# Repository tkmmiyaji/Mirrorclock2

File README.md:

# Mirrorclock2 --- Through the Looking Glass and How the Digital Clock Looks
# 鏡の国のデジタル時計  Ver. 2.2 b 

### by Homebrew and Electronics Lab Cosmic Web, 16 Jul, 2026

## Summary
This repository contains the hardware designs (KiCAD) and the software (AVR assembly language). The hardware design and software are distributed with the Beerware license. See LICENSE.md  

## Hardware

The KiCAD Ver. 10 project files (incl.  kicad_pro, kicad_pcb, and kicad_sch files are included with necessary ./KiCAD.

* AVR: The 28-dip pachage of the Atmega48,88,168,328 and variants should work. 
* The resistor footprints on the PCB accept either THT (3 DIP pitches/7.62mm between holes) or SMD (1206) components. The LED footprints accept 3mm, 5mm diameter ones that have one DIP pitch (2.54mm) between leads. You may be able to place SMD LEDs if you dare.
* Place the tilt switch diagonally, so that the display is stably in the normal mode (see below) when it is placed on a level surface. See ./Gallery/Tilt_Switch_small.jpg.

### Hard-to-find components

* The temperature-compensated Crytsal Module Kyocera KTXO-18 (12.8MHz) or Mercury VCTCXO VM39S5G is used. The latter can be purchased at Akizuki Denshi Tsuusho in Akihabara, Tokyo (https://akizukidenshi.com/catalog/g/g107275/) (availbale as of July, 2026). There may be easier-to find equivalent SMD parts, but to use these a modification in the PCB footprint is required.  

## Software AVRClock2

This software is written in the assmbly language and can be compiled with avra (https://github.com/Ro5bert/avra) and uploaded to the chip using avrdude (https://github.com/avrdudes/avrdude/), both included in the standard repositories of many Linux distros.

### How to Compile/Install (Linux)
* Install avrdude and avra to your system.
* Connect an ISP programmer to the ISP header (6-pin) on board. Watch the orientation. Match the ISP connector bump to that of the PCB drawing.
* Go to directory: ./AVRA
* Open Makefile in your editor and edit the lines with "MCU_TARGET =" and "PROGRAMMER =" to your chip and programmer respectively. Check the port where the programmer is connected and adjust the PORT=/dev/ttyUSB0 line if needed.
* Also the LED brightness auto-adjustment parameters can be set by editing "FA_LIM =" and "BR_LIM =" lines. See Makefile comments for more explanations. 
* From the shell: <br>
SHELL>make                # This compiles the program. <br>
SHELL>make install        # This installs (uploads) the binary to the chip. <br>

## Usage Instructions 
* Connect an external 12V power source.
* It is highly recommended to connect a 9V rectangular battery (called 006P in Japan) for time backup.
* When the unit turns on or reset with the RST button, the clock displays 00:00 00. The clock starts running.
* __Time Adjustment:__ There are three buttons aligned vertically. With a long (~2 sec) push of the central button (MODE), the system enters the hour adjustment mode. Dots in the hour zone blink. You can adjust hours by pushing the upper (ADJ_FWD) and/or lower (ADJ_BWD) buttons. One more pressing of the central button leads to the minute adjustment mode. Dots in the minute zone blink. Use the ADJ_FWD and/or ADJ_BWD buttons to adjust the minute. Note that a long push **will not** make the forward/backward move fast. Whenever the minute is changed, the second zone is reset to zero. When you want to adjust the clock to a second level, push the ADJ_FWD/ADJ_BWD button at the exact moment the reference clock ticks a zero second.
* One more push of the MODE will return the clock to the normal mode.
* __LED Check:__ In the normal mode, pressing the upper button will turn on all the LEDs.
* LED brightness changes responding to the ambient brightness. A press of the lower button shows some calibration and brightness information. There is a trimpot for limited adjustments of the ambient-to-LED brightness relation. Wider range of adjustment is possible in the software (See above).
* __Normal Mode:__ When the clock is right-side up or on a level surface (i.e. the HH:MM display is above the circuts), it displays the clock normally.
* __Mirror Mode: Turn the clock upside down and look through a mirror!__ The roles of ADJ_FWD and ADJ_BWD buttons are also exchanged in the time adjustment.

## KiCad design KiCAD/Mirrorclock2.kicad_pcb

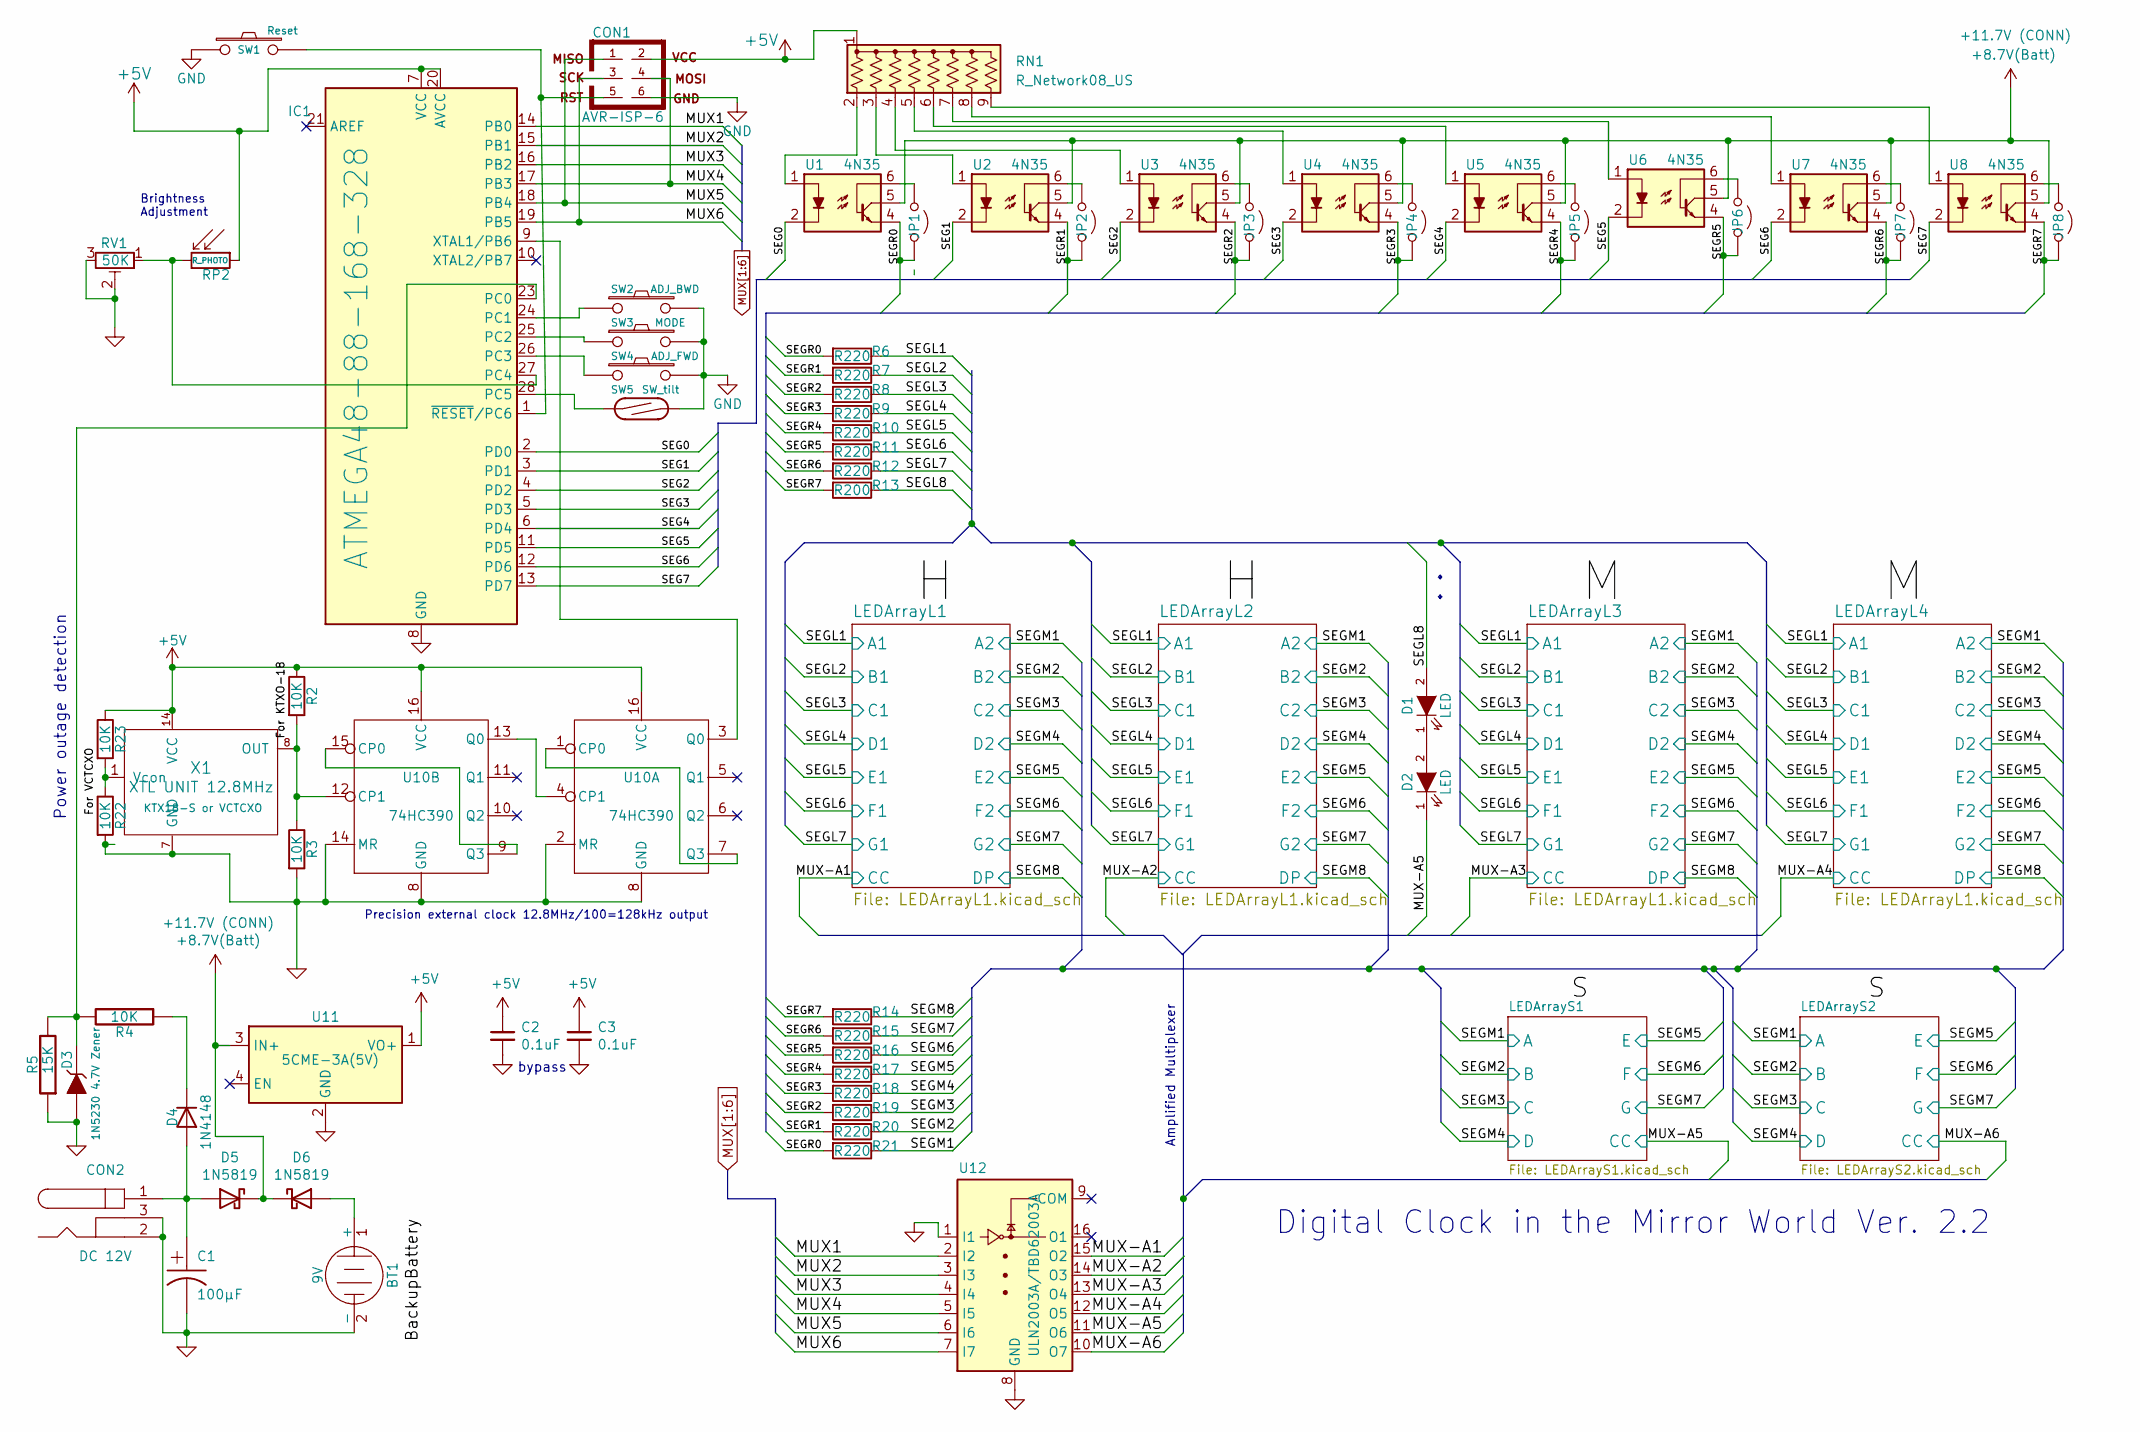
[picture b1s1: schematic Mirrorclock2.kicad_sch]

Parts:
BT1: 9V; PinHeader_1x02_P2.54mm_Vertical
C1: 100μF; CP_Radial_D6.3mm_P2.50mm
C2, C3: 0.1uF; C_Disc_D3.4mm_W2.1mm_P2.50mm
CON1: AVR-ISP-6; AVRISP-6P
CON2: DC 12V; BarrelJack_Horizontal
D1, D2: LED; LED_MULTI
D3: 1N5230 4.7V Zener; D_DO-34_SOD68_P7.62mm_Horizontal
D4: 1N4148; D_DO-35_SOD27_P7.62mm_Horizontal
D5, D6: 1N5819; D_DO-41_SOD81_P7.62mm_Horizontal
IC1: ATMEGA48-88-168-328; DIP-28_W7.62mm
JP1, JP2, JP3, JP4, JP5, JP6, JP7, JP8: Jumper_2_Open; SolderJumper-2_P1.3mm_Open_RoundedPad1.0x1.5mm
R2, R3, R4, R22, R23: 10K; R_THT_SMD1206
R5: 15K; R_THT_SMD1206
R6, R7, R8, R9, R10, R11, R12, R14, R15, R16, R17, R18, R19, R20, R21: R220; R_THT_SMD1206
R13: R200; R_THT_SMD1206
RN1: R_Network08_US; R_Array_SIP9
RP2: R_PHOTO; R_LDR_5.1x4.3mm_P3.4mm_Vertical
RV1: 50K; Potentiometer_Runtron_RM-065_Vertical
SW1: Reset; SW_PUSH_6mm
SW2: ADJ_BWD; SW_PUSH-12mm_Wuerth-430476085716
SW3: MODE; SW_PUSH-12mm_Wuerth-430476085716
SW4: ADJ_FWD; SW_PUSH-12mm_Wuerth-430476085716
SW5: SW_tilt; Sw_tilt_holes
U1, U2, U3, U4, U5, U6, U7, U8: 4N35; DIP-6_W7.62mm
U10: 74HC390; DIP-16_W7.62mm
U11: 5CME-3A(5V); DCDC-Module-Drok
U12: ULN2003A/TBD62003A; DIP-16_W7.62mm
X1: XTL UNIT 12.8MHz; Crystal_M39S_KTXO18; Part KTX18-S or VCTCXO

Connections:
+5V: C2.1, C3.1, CON1.2, IC1.7 (VCC), IC1.20 (AVCC), R2.1, R23.1, RN1.1 (common), RP2.1, U10.16 (VCC), U11.1 (VO+), X1.14 (VCC)
+12V: D5.1 (K), D6.1 (K), U1.5, U2.5, U3.5, U4.5, U5.5, U6.5, U7.5, U8.5, U11.3 (IN+)
/MUX1: IC1.14 (PB0), U12.2 (I2)
/MUX2: IC1.15 (PB1), U12.3 (I3)
/MUX3: IC1.16 (PB2), U12.4 (I4)
/MUX4: CON1.4, IC1.17 (PB3), U12.5 (I5)
/MUX5: CON1.1, IC1.18 (PB4), U12.6 (I6)
/MUX6: CON1.3, IC1.19 (PB5), U12.7 (I7)
/MUX-A1: U12.15 (O2); also elsewhere on the board
/MUX-A2: U12.14 (O3); also elsewhere on the board
/MUX-A3: U12.13 (O4); also elsewhere on the board
/MUX-A4: U12.12 (O5); also elsewhere on the board
/MUX-A5: D2.1 (K), U12.11 (O6); also elsewhere on the board
/MUX-A6: U12.10 (O7); also elsewhere on the board
/SEG0: IC1.2 (PD0), U1.2
/SEG1: IC1.3 (PD1), U2.2
/SEG2: IC1.4 (PD2), U3.2
/SEG3: IC1.5 (PD3), U4.2
/SEG4: IC1.6 (PD4), U5.2
/SEG5: IC1.11 (PD5), U6.2
/SEG6: IC1.12 (PD6), U7.2
/SEG7: IC1.13 (PD7), U8.2
/SEGL1: R6.1; also elsewhere on the board
/SEGL2: R7.1; also elsewhere on the board
/SEGL3: R8.1; also elsewhere on the board
/SEGL4: R9.1; also elsewhere on the board
/SEGL5: R10.1; also elsewhere on the board
/SEGL6: R11.1; also elsewhere on the board
/SEGL7: R12.1; also elsewhere on the board
/SEGL8: D1.2 (A), R13.1
/SEGM1: R21.1; also elsewhere on the board
/SEGM2: R20.1; also elsewhere on the board
/SEGM3: R19.1; also elsewhere on the board
/SEGM4: R18.1; also elsewhere on the board
/SEGM5: R17.1; also elsewhere on the board
/SEGM6: R16.1; also elsewhere on the board
/SEGM7: R15.1; also elsewhere on the board
/SEGM8: R14.1; also elsewhere on the board
/SEGR0: JP1.2 (B), R6.2, R21.2, U1.4
/SEGR1: JP2.2 (B), R7.2, R20.2, U2.4
/SEGR2: JP3.2 (B), R8.2, R19.2, U3.4
/SEGR3: JP4.2 (B), R9.2, R18.2, U4.4
/SEGR4: JP5.2 (B), R10.2, R17.2, U5.4
/SEGR5: JP6.2 (B), R11.2, R16.2, U6.4
/SEGR6: JP7.2 (B), R12.2, R15.2, U7.4
/SEGR7: JP8.2 (B), R13.2, R14.2, U8.4
GND: BT1.2 (-), C1.2, C2.2, C3.2, CON1.6, CON2.2, CON2.3, D3.2 (A), IC1.8 (GND), IC1.22 (GND), R3.2, R5.1, R22.2, RV1.2, RV1.3, SW1.1, SW2.2, SW3.2, SW4.2, SW5.2, U10.2 (MR), U10.8 (GND), U10.14 (MR), U11.2 (GND), U12.1 (I1), U12.8 (GND), X1.7 (GND)
unnamed: BT1.1 (+), D6.2 (A)
unnamed: D1.1 (K), D2.2 (A)
unnamed: D3.1 (K), IC1.23 (PC0), R4.2, R5.2
unnamed: C1.1, CON2.1, D4.2 (A), D5.2 (A)
unnamed: D4.1 (K), R4.1
unnamed: IC1.24 (PC1), SW2.1
unnamed: IC1.25 (PC2), SW3.1
unnamed: IC1.26 (PC3), SW4.1
unnamed: IC1.9 (XTAL1/PB6), U10.3 (Q0)
unnamed: CON1.5, IC1.1 (~RESET/PC6), SW1.2
unnamed: JP1.1 (A), U1.6
unnamed: JP2.1 (A), U2.6
unnamed: JP3.1 (A), U3.6
unnamed: JP4.1 (A), U4.6
unnamed: JP5.1 (A), U5.6
unnamed: JP6.1 (A), U6.6
unnamed: JP7.1 (A), U7.6
unnamed: JP8.1 (A), U8.6
unnamed: RN1.2 (R1), U1.1
unnamed: RN1.3 (R2), U2.1
unnamed: RN1.4 (R3), U3.1
unnamed: RN1.5 (R4), U4.1
unnamed: RN1.6 (R5), U5.1
unnamed: RN1.7 (R6), U6.1
unnamed: RN1.8 (R7), U7.1
unnamed: RN1.9 (R8), U8.1
unnamed: U10.1 (CP0), U10.7 (Q3)
unnamed: U10.4 (CP1), U10.13 (Q0)
unnamed: U10.9 (Q3), U10.15 (CP0)
unnamed: R2.2, R3.1, U10.12 (CP1), X1.8 (OUT)
unnamed: R22.1, R23.2, X1.1 (Vcon)

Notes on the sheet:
Digital Clock in the Mirror World Ver. 2.2
Precision external clock 12.8MHz/100=128kHz output
Brightness Adjustment
Amplified Multiplexer
bypass
Power outage detection

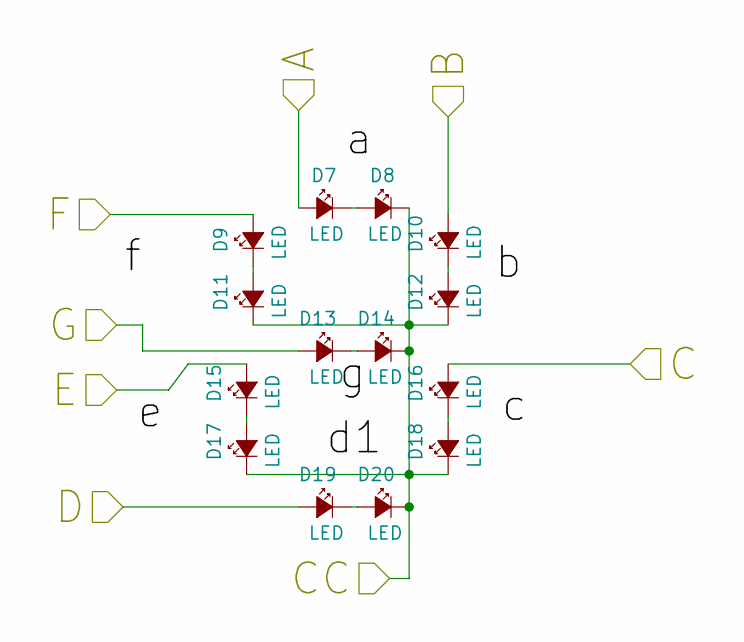
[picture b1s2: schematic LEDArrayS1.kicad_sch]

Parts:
D7, D8, D9, D10, D11, D12, D13, D14, D15, D16, D17, D18, D19, D20: LED; LED_MULTI

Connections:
/MUX-A5: D8.1 (K), D11.1 (K), D12.1 (K), D14.1 (K), D17.1 (K), D18.1 (K), D20.1 (K); also elsewhere on the board
/SEGM1: D7.2 (A); also elsewhere on the board
/SEGM2: D10.2 (A); also elsewhere on the board
/SEGM3: D16.2 (A); also elsewhere on the board
/SEGM4: D19.2 (A); also elsewhere on the board
/SEGM5: D15.2 (A); also elsewhere on the board
/SEGM6: D9.2 (A); also elsewhere on the board
/SEGM7: D13.2 (A); also elsewhere on the board
unnamed: D7.1 (K), D8.2 (A)
unnamed: D10.1 (K), D12.2 (A)
unnamed: D9.1 (K), D11.2 (A)
unnamed: D13.1 (K), D14.2 (A)
unnamed: D15.1 (K), D17.2 (A)
unnamed: D16.1 (K), D18.2 (A)
unnamed: D19.1 (K), D20.2 (A)

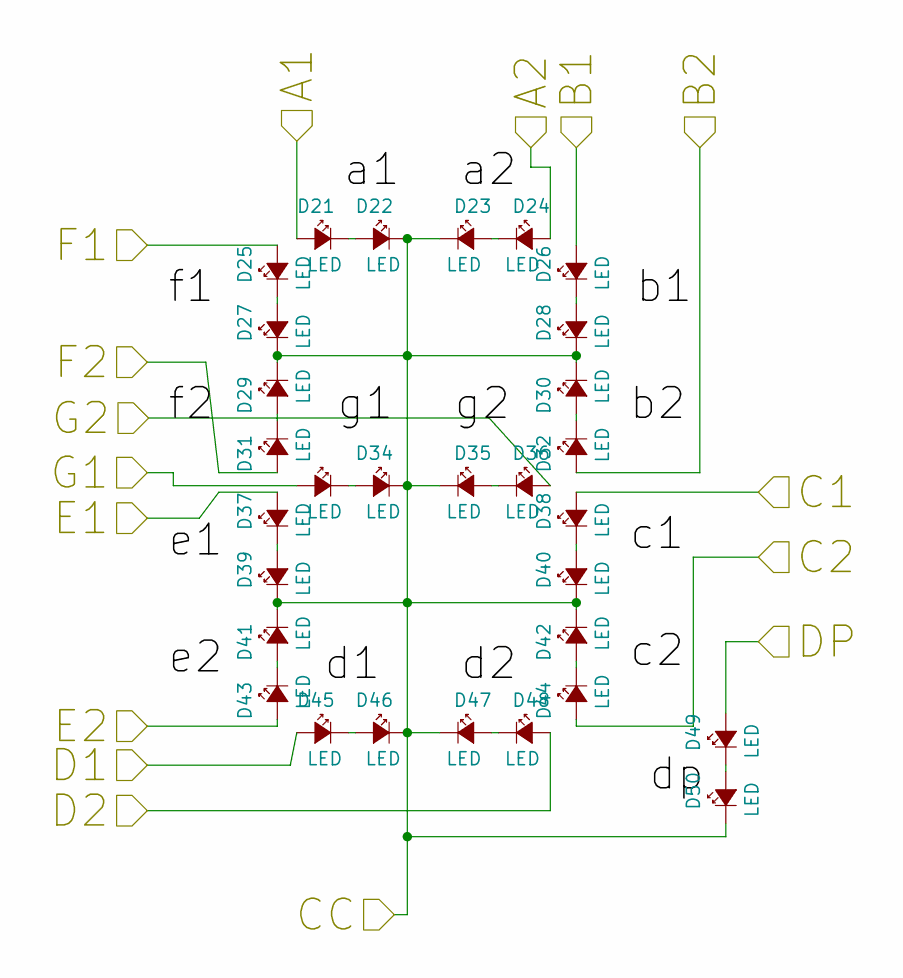
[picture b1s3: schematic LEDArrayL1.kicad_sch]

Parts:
D21, D22, D23, D24, D25, D26, D27, D28, D29, D30, D31, D32, D33, D34, D35, D36, D37, D38, D39, D40, D41, D42, D43, D44, D45, D46, D47, D48: LED; LED_MULTI
D49, D50: LED; LED_MULTI_SIMPLE

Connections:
/MUX-A1: D22.1 (K), D23.1 (K), D27.1 (K), D28.1 (K), D29.1 (K), D30.1 (K), D34.1 (K), D35.1 (K), D39.1 (K), D40.1 (K), D41.1 (K), D42.1 (K), D46.1 (K), D47.1 (K), D50.1 (K); also elsewhere on the board
/SEGL1: D21.2 (A); also elsewhere on the board
/SEGL2: D26.2 (A); also elsewhere on the board
/SEGL3: D38.2 (A); also elsewhere on the board
/SEGL4: D45.2 (A); also elsewhere on the board
/SEGL5: D37.2 (A); also elsewhere on the board
/SEGL6: D25.2 (A); also elsewhere on the board
/SEGL7: D33.2 (A); also elsewhere on the board
/SEGM1: D24.2 (A); also elsewhere on the board
/SEGM2: D32.2 (A); also elsewhere on the board
/SEGM3: D44.2 (A); also elsewhere on the board
/SEGM4: D48.2 (A); also elsewhere on the board
/SEGM5: D43.2 (A); also elsewhere on the board
/SEGM6: D31.2 (A); also elsewhere on the board
/SEGM7: D36.2 (A); also elsewhere on the board
/SEGM8: D49.2 (A); also elsewhere on the board
unnamed: D21.1 (K), D22.2 (A)
unnamed: D23.2 (A), D24.1 (K)
unnamed: D25.1 (K), D27.2 (A)
unnamed: D26.1 (K), D28.2 (A)
unnamed: D29.2 (A), D31.1 (K)
unnamed: D30.2 (A), D32.1 (K)
unnamed: D33.1 (K), D34.2 (A)
unnamed: D35.2 (A), D36.1 (K)
unnamed: D37.1 (K), D39.2 (A)
unnamed: D38.1 (K), D40.2 (A)
unnamed: D41.2 (A), D43.1 (K)
unnamed: D42.2 (A), D44.1 (K)
unnamed: D45.1 (K), D46.2 (A)
unnamed: D47.2 (A), D48.1 (K)
unnamed: D49.1 (K), D50.2 (A)

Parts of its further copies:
D51, D52, D53, D54, D55, D56, D57, D58, D59, D60, D61, D62, D63, D64, D65, D66, D67, D68, D69, D70, D71, D72, D73, D74, D75, D76, D77, D78, D81, D82, D83, D84, D85, D86, D87, D88, D89, D90, D91, D92, D93, D94, D95, D96, D97, D98, D99, D100, D101, D102, D103, D104, D105, D106, D107, D108, D111, D112, D113, D114, D115, D116, D117, D118, D119, D120, D121, D122, D123, D124, D125, D126, D127, D128, D129, D130, D131, D132, D133, D134, D135, D136, D137, D138: LED; LED_MULTI
D79, D80, D109, D110, D139, D140: LED; LED_MULTI_SIMPLE

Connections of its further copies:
/MUX-A2: D52.1 (K), D53.1 (K), D57.1 (K), D58.1 (K), D59.1 (K), D60.1 (K), D64.1 (K), D65.1 (K), D69.1 (K), D70.1 (K), D71.1 (K), D72.1 (K), D76.1 (K), D77.1 (K), D80.1 (K); also elsewhere on the board
/MUX-A3: D82.1 (K), D83.1 (K), D87.1 (K), D88.1 (K), D89.1 (K), D90.1 (K), D94.1 (K), D95.1 (K), D99.1 (K), D100.1 (K), D101.1 (K), D102.1 (K), D106.1 (K), D107.1 (K), D110.1 (K); also elsewhere on the board
/MUX-A4: D112.1 (K), D113.1 (K), D117.1 (K), D118.1 (K), D119.1 (K), D120.1 (K), D124.1 (K), D125.1 (K), D129.1 (K), D130.1 (K), D131.1 (K), D132.1 (K), D136.1 (K), D137.1 (K), D140.1 (K); also elsewhere on the board
/SEGL1: D51.2 (A), D81.2 (A), D111.2 (A); also elsewhere on the board
/SEGL2: D56.2 (A), D86.2 (A), D116.2 (A); also elsewhere on the board
/SEGL3: D68.2 (A), D98.2 (A), D128.2 (A); also elsewhere on the board
/SEGL4: D75.2 (A), D105.2 (A), D135.2 (A); also elsewhere on the board
/SEGL5: D67.2 (A), D97.2 (A), D127.2 (A); also elsewhere on the board
/SEGL6: D55.2 (A), D85.2 (A), D115.2 (A); also elsewhere on the board
/SEGL7: D63.2 (A), D93.2 (A), D123.2 (A); also elsewhere on the board
/SEGM1: D54.2 (A), D84.2 (A), D114.2 (A); also elsewhere on the board
/SEGM2: D62.2 (A), D92.2 (A), D122.2 (A); also elsewhere on the board
/SEGM3: D74.2 (A), D104.2 (A), D134.2 (A); also elsewhere on the board
/SEGM4: D78.2 (A), D108.2 (A), D138.2 (A); also elsewhere on the board
/SEGM5: D73.2 (A), D103.2 (A), D133.2 (A); also elsewhere on the board
/SEGM6: D61.2 (A), D91.2 (A), D121.2 (A); also elsewhere on the board
/SEGM7: D66.2 (A), D96.2 (A), D126.2 (A); also elsewhere on the board
/SEGM8: D79.2 (A), D109.2 (A), D139.2 (A); also elsewhere on the board
unnamed: D51.1 (K), D52.2 (A)
unnamed: D53.2 (A), D54.1 (K)
unnamed: D55.1 (K), D57.2 (A)
unnamed: D56.1 (K), D58.2 (A)
unnamed: D59.2 (A), D61.1 (K)
unnamed: D60.2 (A), D62.1 (K)
unnamed: D63.1 (K), D64.2 (A)
unnamed: D65.2 (A), D66.1 (K)
unnamed: D67.1 (K), D69.2 (A)
unnamed: D68.1 (K), D70.2 (A)
unnamed: D71.2 (A), D73.1 (K)
unnamed: D72.2 (A), D74.1 (K)
unnamed: D75.1 (K), D76.2 (A)
unnamed: D77.2 (A), D78.1 (K)
unnamed: D79.1 (K), D80.2 (A)
unnamed: D81.1 (K), D82.2 (A)
unnamed: D83.2 (A), D84.1 (K)
unnamed: D85.1 (K), D87.2 (A)
unnamed: D86.1 (K), D88.2 (A)
unnamed: D89.2 (A), D91.1 (K)
unnamed: D90.2 (A), D92.1 (K)
unnamed: D93.1 (K), D94.2 (A)
unnamed: D95.2 (A), D96.1 (K)
unnamed: D97.1 (K), D99.2 (A)
unnamed: D98.1 (K), D100.2 (A)
unnamed: D101.2 (A), D103.1 (K)
unnamed: D102.2 (A), D104.1 (K)
unnamed: D105.1 (K), D106.2 (A)
unnamed: D107.2 (A), D108.1 (K)
unnamed: D109.1 (K), D110.2 (A)
unnamed: D111.1 (K), D112.2 (A)
unnamed: D113.2 (A), D114.1 (K)
unnamed: D115.1 (K), D117.2 (A)
unnamed: D116.1 (K), D118.2 (A)
unnamed: D119.2 (A), D121.1 (K)
unnamed: D120.2 (A), D122.1 (K)
unnamed: D123.1 (K), D124.2 (A)
unnamed: D125.2 (A), D126.1 (K)
unnamed: D127.1 (K), D129.2 (A)
unnamed: D128.1 (K), D130.2 (A)
unnamed: D131.2 (A), D133.1 (K)
unnamed: D132.2 (A), D134.1 (K)
unnamed: D135.1 (K), D136.2 (A)
unnamed: D137.2 (A), D138.1 (K)
unnamed: D139.1 (K), D140.2 (A)

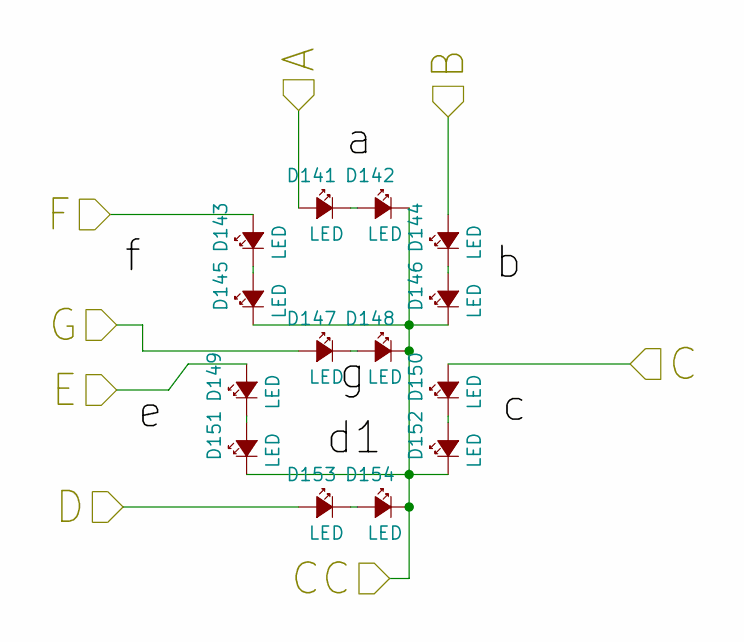
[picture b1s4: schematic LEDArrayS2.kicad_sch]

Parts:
D141, D142, D143, D144, D145, D146, D147, D148, D149, D150, D151, D152, D153, D154: LED; LED_MULTI

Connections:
/MUX-A6: D142.1 (K), D145.1 (K), D146.1 (K), D148.1 (K), D151.1 (K), D152.1 (K), D154.1 (K); also elsewhere on the board
/SEGM1: D141.2 (A); also elsewhere on the board
/SEGM2: D144.2 (A); also elsewhere on the board
/SEGM3: D150.2 (A); also elsewhere on the board
/SEGM4: D153.2 (A); also elsewhere on the board
/SEGM5: D149.2 (A); also elsewhere on the board
/SEGM6: D143.2 (A); also elsewhere on the board
/SEGM7: D147.2 (A); also elsewhere on the board
unnamed: D141.1 (K), D142.2 (A)
unnamed: D143.1 (K), D145.2 (A)
unnamed: D144.1 (K), D146.2 (A)
unnamed: D147.1 (K), D148.2 (A)
unnamed: D149.1 (K), D151.2 (A)
unnamed: D150.1 (K), D152.2 (A)
unnamed: D153.1 (K), D154.2 (A)

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
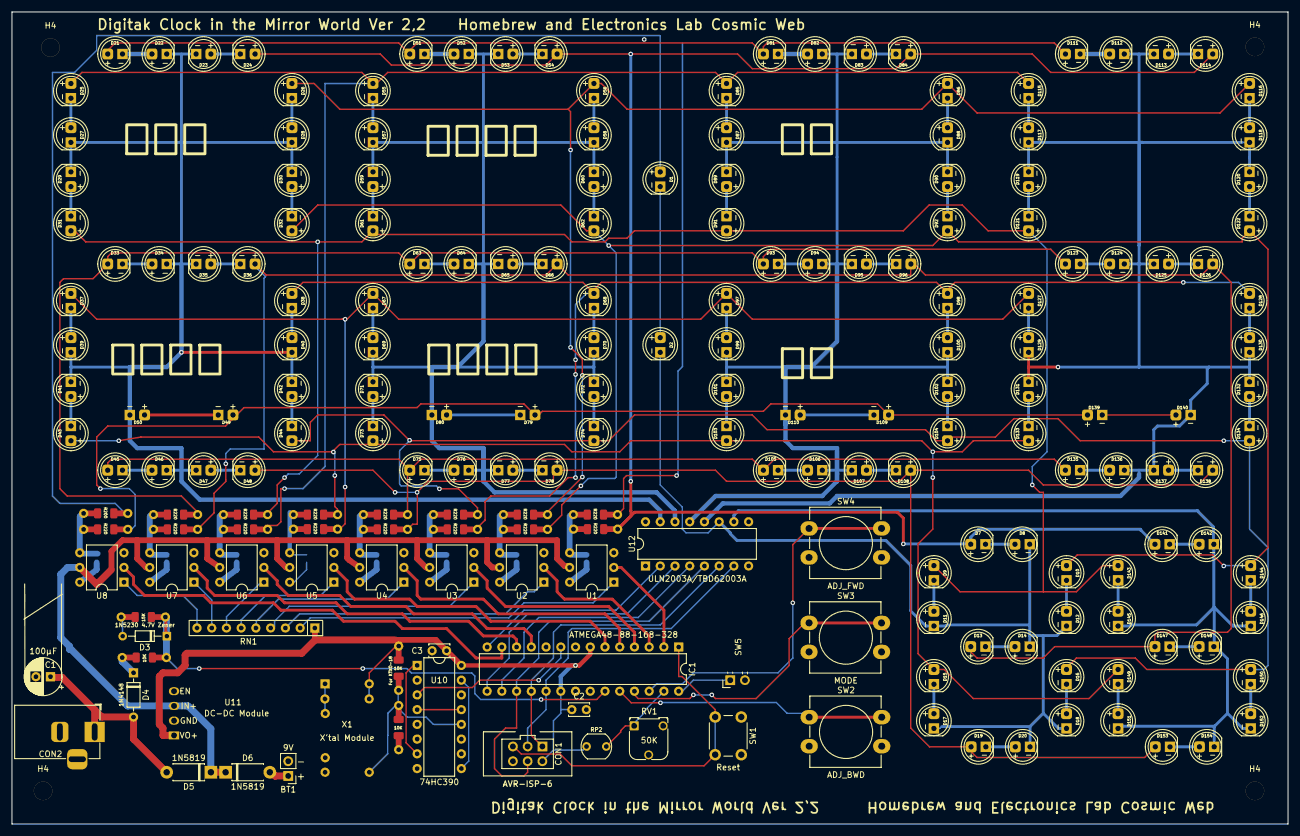
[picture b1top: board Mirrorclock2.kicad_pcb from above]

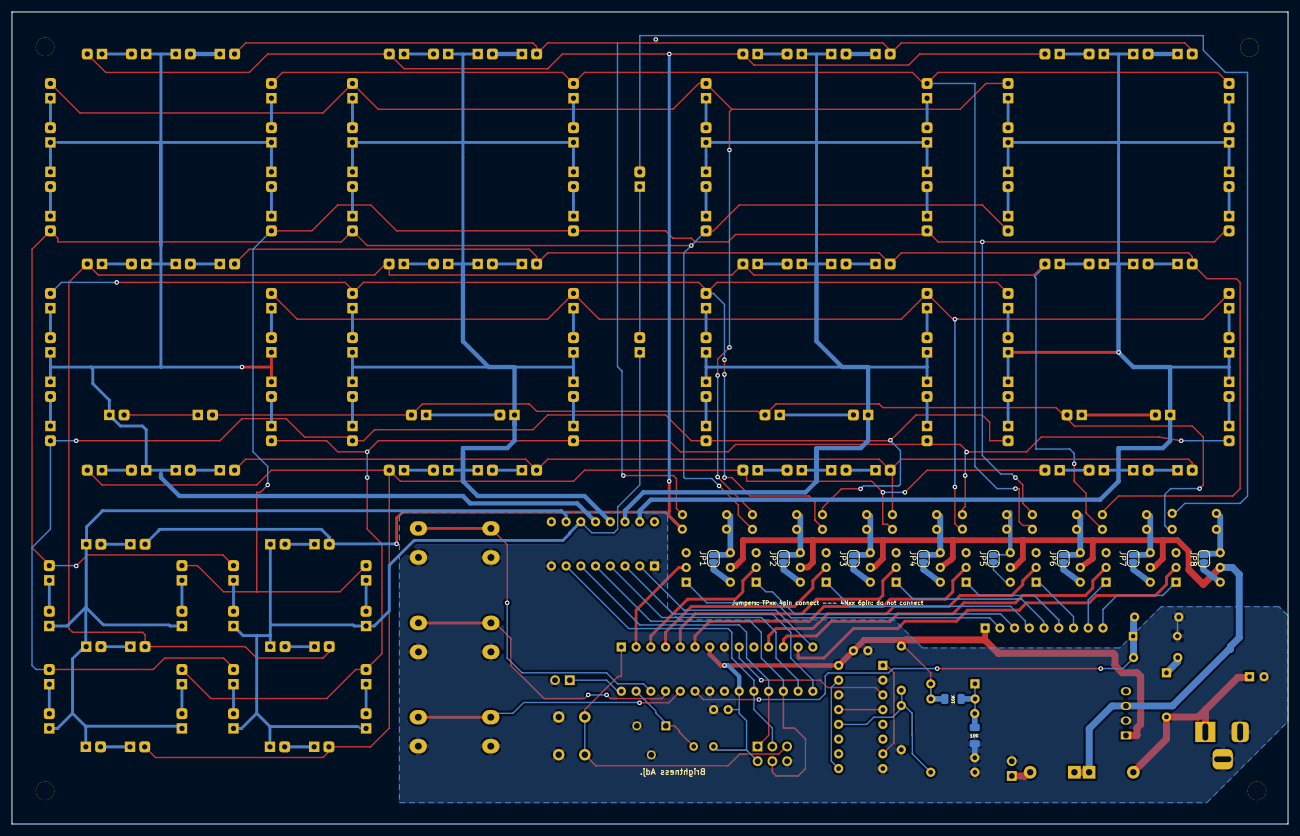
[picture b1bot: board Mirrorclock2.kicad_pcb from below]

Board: 2 copper layers, 220.0 x 140.0 mm, 215 parts (10 on the bottom side), 153 nets.

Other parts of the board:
H4, H4#2, H4#3, H4#4: MountingHole; MountingHole_3.2mm_M3_ISO7380

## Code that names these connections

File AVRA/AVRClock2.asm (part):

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		;;
		;;	Configure Input Pins
		;;
		;;   PC0-Externally Pulled Down, Power Outage detection	
		;;   PC3-Pullup  : Upper Botton  Adjust Up (normal) Down (mirrored)/Enforce Wake  
		;;   PC2-Pullup  : Middle Button  Mode Display -push_1sec ->Hr Adj ->Min Adj->Display
		;;   PC1-Pullup  : Lower Botton  Adjust Down (normal) Up (mirrored)/Enforce Wake
		;;
		;;   PC5-Pullup  : Tilt Detector  
		;;
		ldi	A, 	0b00000000	
		out	DDRC, A
		ldi	A,	0b00101110	 
		out	PORTC, A
		nop
		;;   PC4-ADC4    : Brightness Detector Configure as ADC
		clr	A
		ldi	A,	(1<<ADC4D) ; Disabe digital input for ADC 4 
		sts	DIDR0, A		
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		sts	ADCSRA, A
		;;
		;;	*****   Output Pin Configuration  **** 
		;;   	PD0-7: Output Pin ... 7 Seg
		;;   	PB0-5: Output Pin ... 6 digit Multiplexer
		;;	
		ldi	A,	0xFF
		out	DDRD, 	A	
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		ldi	XL,	low(SEGM_NO<<1)
		ldi	XH,	high(SEGM_NO<<1)
		in	A, 	PINC							
		andi	A,	(1<<TILT)	; See Port PC5 (Tilt Switch)  to decide Normal(0) or Mirrored (1)
		breq	skip_mirror
		ldi	XL,	low(SEGM_MR<<1)
		ldi	XH,	high(SEGM_MR<<1)
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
